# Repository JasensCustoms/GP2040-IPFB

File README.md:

The <a href="https://jasenscustoms.com/collections/fight-stick-pcbs/products/integrated-pico-fighting-board-gp2040ce">Integrated Pico Fighting Board</a> is an open source arcade fight stick PCB design made available under the Creative Commons Attribution-Non Commercial Sharealike 4.0 International License. This is a solely **hardware** project that is designed to easily run **unmodified** GP2040-CE firmware. That has always been the intent despite narratives suggesting otherwise.

It was designed to follow the Fighting Game Community Layout Generally Accepted Standard originally pioneered by AkiShop. This design was adopted by Brook for most of their fighting boards at the behest and urging of myself and a few other makers in the space early in Brook's entry to the market. The goal was to make the IPFB a low cost, easy drop-in in replacement for the PS360+ or any Brook Board if a person so chose.

## Design Files

All design files are made using Autodesk EagleCAD and will only be published in that format. Gerbers and Centroids will not be provided. A basic BOM will also be provided. This is to allow hobbyists with some design experience to use their choice of board house to produce their PCBs. There are many to chose from, and it is not our intent to influence your choice. All files are provided as-is without any guarantee of support or help. 

## Sale Channels

Note: The only entity that may sell the Integrated Pico Fighting Board Design is at the link above. If you wish to offer this design commercially, please reach out to [jasenhicks@jasenscustoms.com ](mailto:jasenhicks@jasenscustoms.com). If others are approved to sell the design, they will be listed here. I encourage you to inform me if you see unapproved commercial sale of the IPFB. As of now, I have chosen to stop production of the IPFB. A full discussion can be found on our discord, linked below.

## GPIO Settings 

Main Buttons and Directions:

- GPIO 0: Left
- GPIO 1: Up
- GPIO 2: Down
- GPIO 3: Right
- GPIO 4: HOME (PS)
- GPIO 5: SELECT (SHARE)
- GPIO 6: START
- GPIO 7: Punch 1
- GPIO 8: Punch 2
- GPIO 9: Punch 3
- GPIO 10: Punch 4
- GPIO 11: Kick 1
- GPIO 12: Kick 2
- GPIO 13: Kick 3
- GPIO 14: Kick 4

RGB Data Channel

- GPIO 15: RGB Data

Player LEDS (Version 2.0+ PCB can designate these as other functions as the resistor on the line has been removed)

- GPIO 16: Player 1 LED
- GPIO 17: Player 2 LED
- GPIO 18: Player 3 LED
- GPIO 19: Player 4 LED

Modern Controller Buttons, Turbo Functions

- GPIO 20: Touch Pad Click
- GPIO 21: L3
- GPIO 22: R3
- GPIO 23: TURBO LED (Version 2.0+ PCB can designate this as another function as the resistor on the line has been removed)
- GPIO 28: TURBO KEY

I2C Lines both have been pulled high via resistor (3.3V)

- GPIO 26: SDA
- GPIO 27: SCL

USB Passthrough GPIO

- GPIO 24: DATA PLUS
- GPIO 25: DATA MINUS

## Firmware

No custom firmware is needed or provided for the Integrated Pico Fighting Board. Because the pin definitions are derived from FeralAI's carrier board, firmware for the Pico Fighting Board is expected to be compatible with minimal settings changes. Steps to customize GP2040-CE settings to fully utilize Turbo and Playstation authentication are indicated below.

### Settings
To manually adust the PicoFightingBoard firmware to work perfectly with the IPFB, just adjust these settings.

#### Turbo
- Add on Configuration:
  - Enable turbo
  - Turbo LED Pin 23
  - Save
- Pin Mappings:
  - Set pin 28 to Turbo
  - Save

#### PS5 (or PS4)
- Input Mode Settings
  - Current Input Mode: PS5 (or PS4)
  - Authentication Settings: Host USB
- Boot Input Modes
  - Set B4 to PS5 (or PS4)

#### XBone
- Boot Input Modes
  - Set R1 to XBone

## Support

All files are provided as is and without warranty.

For issues with Integrated Pico Fight Board hardware that was bought and sold via JasensCustoms.com, please reach out via [Jasen's Customs Discord](https://discord.gg/M9E8PFHSCm).

To discuss GP2040-CE firmware including features, issues, or anything else please join the [OpenStick GP2040-CE Discord](https://discord.gg/k2pxhke7q8) or [create a GitHub issue](https://github.com/OpenStickCommunity/GP2040-CE/issues/new).

Hardware change suggestions can be submitted as GitHub issues on this repository, and will be reviewed on a case by case basis by the JasensCustoms.com team. Not all suggestions will be implemented.

## Acknolwedgements

- [RegentOfOrigin](https://github.com/RegentOfOrigin) for helping manage the GitHub
- [wrennnnnn](https://github.com/wrennnnnn). for the initial management and compiling of the FW with the IPFB Config.h file
- [The entire Open Stick Community](https://github.com/OpenStickCommunity) for the GP2040-CE firmware
- Particularly [FeralAI](https://github.com/FeralAI) for the initial work in designing and making the [PicoFightingBoard](https://github.com/FeralAI/PicoFightingBoard) available

Copyright for the Pico Fighting Board is held by FeralAI, 2021.
Copyright for GP2040-CE is held by The Open Stick Community, 2024.

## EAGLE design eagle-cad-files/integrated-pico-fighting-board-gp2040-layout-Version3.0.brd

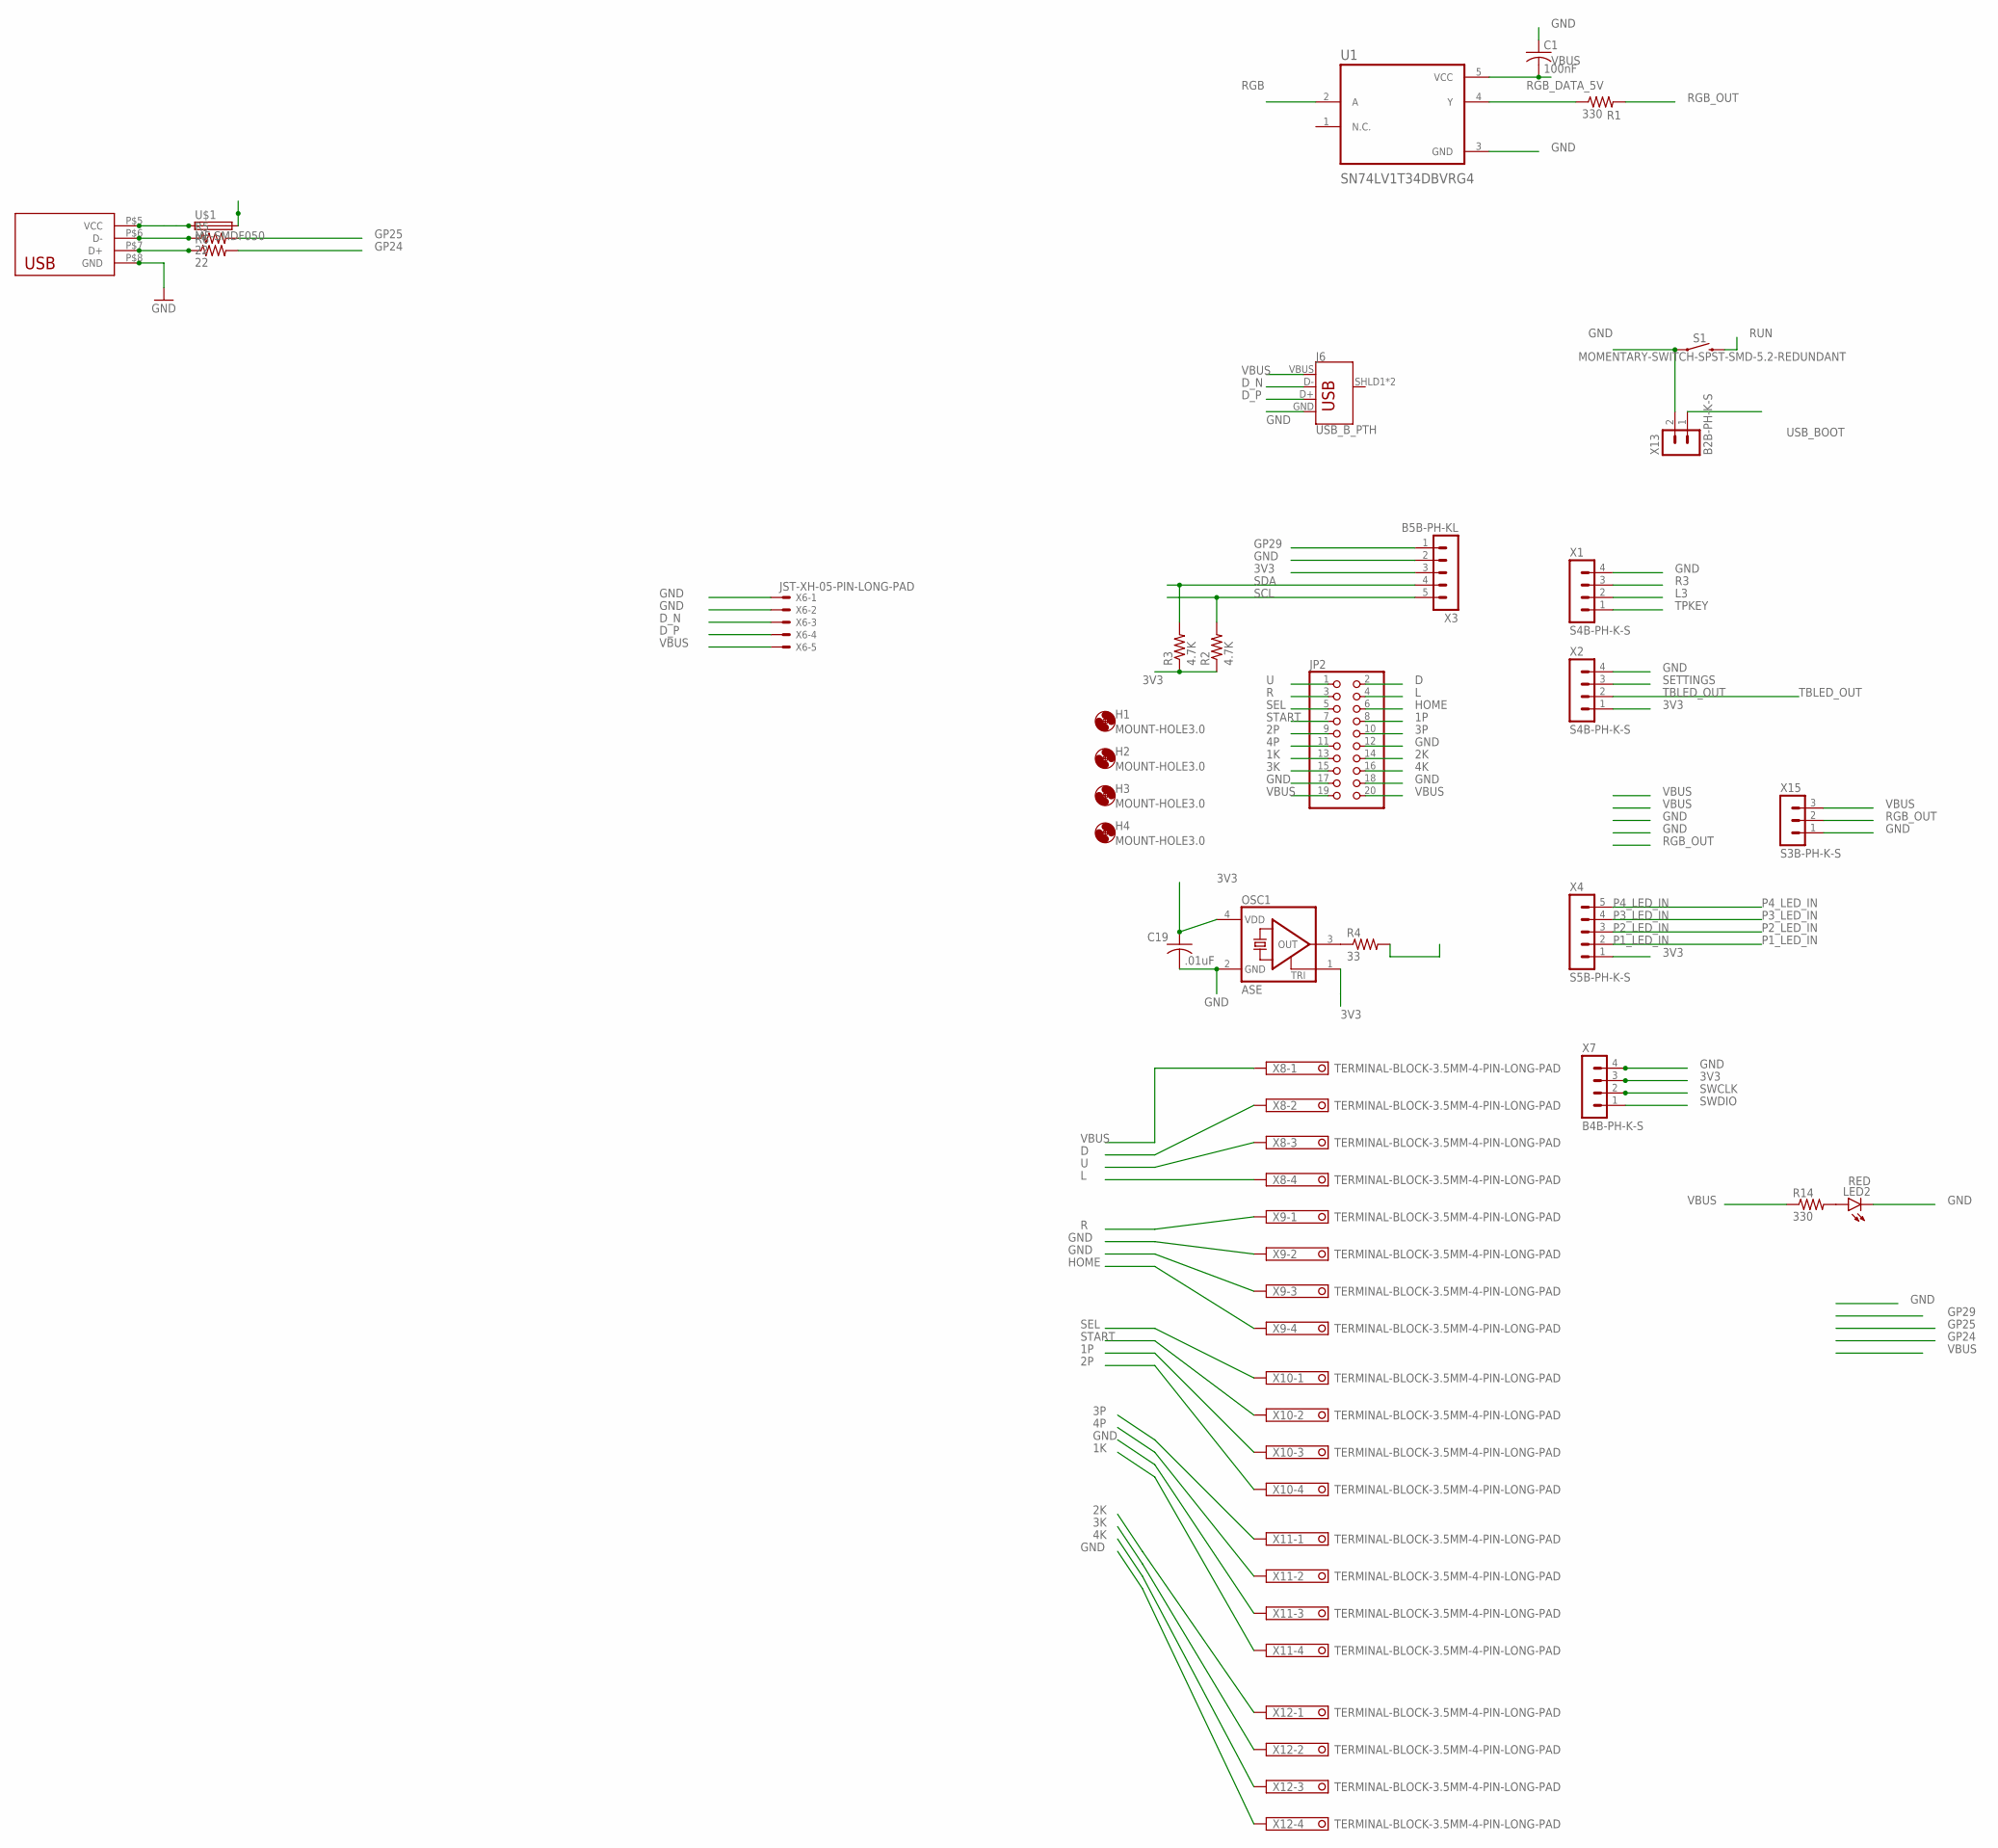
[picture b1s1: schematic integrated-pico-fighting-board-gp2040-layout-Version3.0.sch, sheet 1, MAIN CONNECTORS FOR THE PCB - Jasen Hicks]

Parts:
C1: 100nF; C0603K
C19: .01uF; C0402K
H1, H2, H3, H4: MOUNT-HOLE3.0; 3,0
J6: USB_B_PTH; USB-B-PTH
JP2: PINHD-2X10; 2X10
LED2: RED; CHIP-LED0603
OSC1: ASE
R1, R14: 330; R0603
R2, R3: 4.7K; R0603
R4: 33; R0402
R5, R6: 22; R0805
S1: MOMENTARY-SWITCH-SPST-SMD-5.2-REDUNDANT; TACTILE_SWITCH_SMD_5.2MM
U1: SN74LV1T34DBVRG4; SOT95P280X145-5N
U$1: MF-SMDF050
U$2: USB-302S
X1, X2: S4B-PH-K-S
X3: B5B-PH-KL; B5B-PH-K-S
X4: S5B-PH-K-S
X6: JST-XH-05-PIN-LONG-PAD; JST-XH-05-PACKAGE-LONG-PAD
X7: B4B-PH-K-S
X8, X9, X10, X11, X12: TERMINAL-BLOCK-3.5MM-4-PIN-LONG-PAD; TERMINAL-BLOCK-4-PIN-3.5MM-LONG-PAD
X13: B2B-PH-K-S
X15: S3B-PH-K-S

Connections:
1K: JP2.13, X11.4; also elsewhere on the board
1P: JP2.8, X10.3; also elsewhere on the board
2K: JP2.14, X12.1; also elsewhere on the board
2P: JP2.9, X10.4; also elsewhere on the board
3K: JP2.15, X12.2; also elsewhere on the board
3P: JP2.10, X11.1; also elsewhere on the board
3V3: C19.1, OSC1.1 (TRI), OSC1.4 (VDD), R2.1, R3.1, X2.1, X3.3, X4.1, X7.3; also elsewhere on the board
4K: JP2.16, X12.3; also elsewhere on the board
4P: JP2.11, X11.2; also elsewhere on the board
D: JP2.2, X8.2; also elsewhere on the board
D_N: J6.D-, X6.3; also elsewhere on the board
D_P: J6.D+, X6.4; also elsewhere on the board
GND: C1.1, C19.2, J6.GND, JP2.12, JP2.17, JP2.18, LED2.C, OSC1.2 (GND), S1.1, S1.2 (1), U1.3 (GND), U$2.P$8 (GND), X1.4, X2.4, X3.2, X6.1, X6.2, X7.4, X9.2, X9.3, X11.3, X12.4, X13.2, X15.1; also elsewhere on the board
GP24: R6.2; also elsewhere on the board
GP25: R5.2; also elsewhere on the board
GP29: X3.1; also elsewhere on the board
HOME: JP2.6, X9.4; also elsewhere on the board
L: JP2.4, X8.4; also elsewhere on the board
L3: X1.2; also elsewhere on the board
unnamed: OSC1.3 (OUT), R4.1
unnamed: LED2.A, R14.2
unnamed: U$1.1, U$2.P$5 (VCC)
unnamed: R5.1, U$2.P$6 (D-)
unnamed: R6.1, U$2.P$7 (D+)
P1_LED_IN: X4.2; also elsewhere on the board
P2_LED_IN: X4.3; also elsewhere on the board
P3_LED_IN: X4.4; also elsewhere on the board
P4_LED_IN: X4.5; also elsewhere on the board
R: JP2.3, X9.1; also elsewhere on the board
R3: X1.3; also elsewhere on the board
RGB: U1.2 (A); also elsewhere on the board
RGB_DATA_5V: R1.1, U1.4 (Y)
RGB_OUT: R1.2, X15.2
RUN: S1.3 (2), S1.4 (2); also elsewhere on the board
SCL: R2.2, X3.5; also elsewhere on the board
SDA: R3.2, X3.4; also elsewhere on the board
SEL: JP2.5, X10.1; also elsewhere on the board
SETTINGS: X2.3; also elsewhere on the board
START: JP2.7, X10.2; also elsewhere on the board
SWCLK: X7.2; also elsewhere on the board
SWDIO: X7.1; also elsewhere on the board
TBLED_OUT: X2.2; also elsewhere on the board
TPKEY: X1.1; also elsewhere on the board
U: JP2.1, X8.3; also elsewhere on the board
USB_BOOT: X13.1; also elsewhere on the board
VBUS: C1.2, J6.VBUS, JP2.19, JP2.20, R14.1, U1.5 (VCC), U$1.2, X6.5, X8.1, X15.3; also elsewhere on the board
XIN: R4.2; also elsewhere on the board

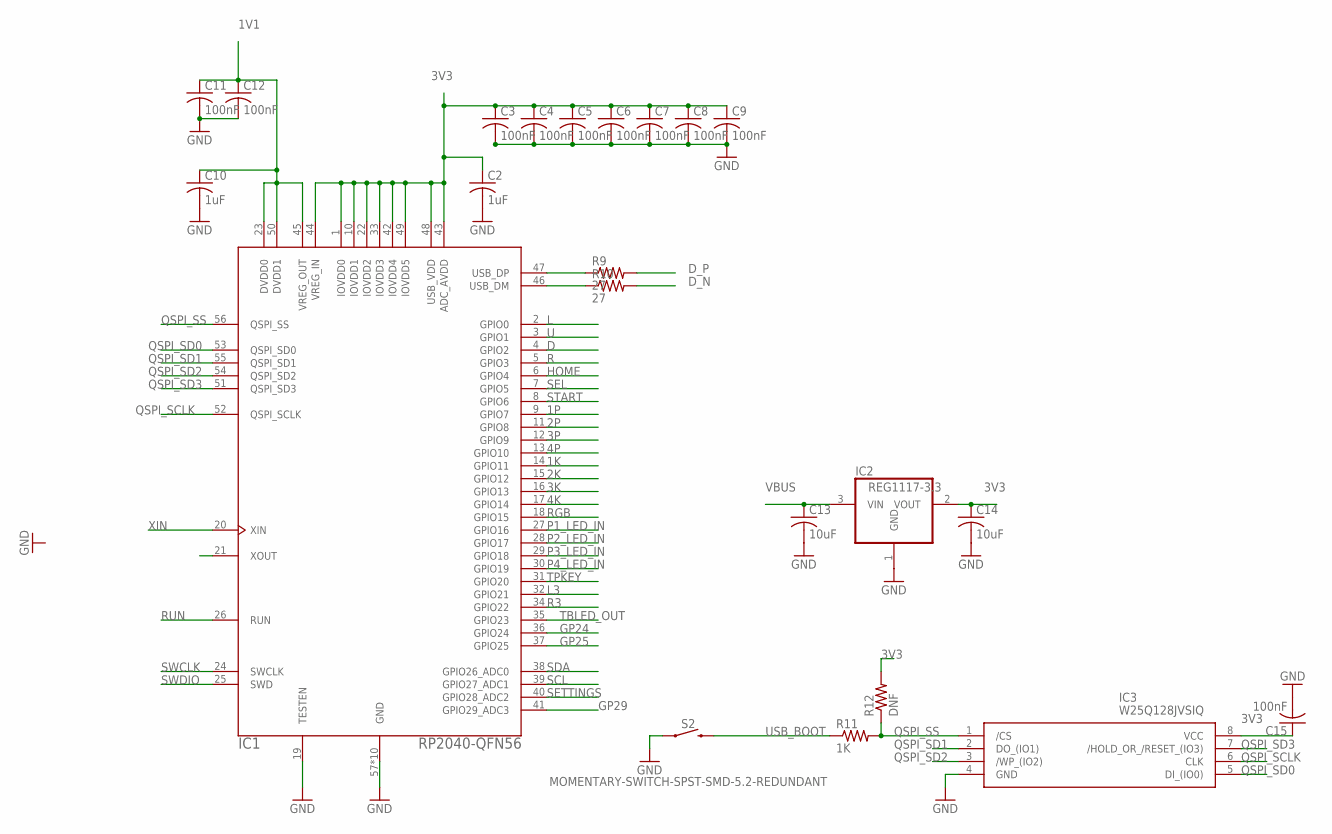
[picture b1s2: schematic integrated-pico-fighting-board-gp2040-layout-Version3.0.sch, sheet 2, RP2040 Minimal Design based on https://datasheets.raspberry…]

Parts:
C2, C10: 1uF; C0402K
C3, C4, C5, C6, C7, C8, C9, C11, C12, C15: 100nF; C0402K
C13, C14: 10uF; C0402K
IC1: RP2040-QFN56; RP2040-QFN-56
IC2: REG1117-3.3; SOT223
IC3: W25Q128JVSIQ; SOIC127P790X216-8N
R9, R10: 27; R0402
R11: 1K; R0402
R12: DNF; R0402
S2: MOMENTARY-SWITCH-SPST-SMD-5.2-REDUNDANT; TACTILE_SWITCH_SMD_5.2MM

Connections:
1K: IC1.14 (GPIO11); also elsewhere on the board
1P: IC1.9 (GPIO7); also elsewhere on the board
1V1: C10.1, C11.1, C12.1, IC1.23 (DVDD0), IC1.45 (VREG_OUT), IC1.50 (DVDD1)
2K: IC1.15 (GPIO12); also elsewhere on the board
2P: IC1.11 (GPIO8); also elsewhere on the board
3K: IC1.16 (GPIO13); also elsewhere on the board
3P: IC1.12 (GPIO9); also elsewhere on the board
3V3: C2.1, C3.1, C4.1, C5.1, C6.1, C7.1, C8.1, C9.1, C14.1, C15.1, IC1.1 (IOVDD0), IC1.10 (IOVDD1), IC1.22 (IOVDD2), IC1.33 (IOVDD3), IC1.42 (IOVDD4), IC1.43 (ADC_AVDD), IC1.44 (VREG_IN), IC1.48 (USB_VDD), IC1.49 (IOVDD5), IC2.2 (VOUT), IC3.8 (VCC), R12.2; also elsewhere on the board
4K: IC1.17 (GPIO14); also elsewhere on the board
4P: IC1.13 (GPIO10); also elsewhere on the board
D: IC1.4 (GPIO2); also elsewhere on the board
D_N: R10.2; also elsewhere on the board
D_P: R9.2; also elsewhere on the board
GND: C2.2, C3.2, C4.2, C5.2, C6.2, C7.2, C8.2, C9.2, C10.2, C11.2, C12.2, C13.2, C14.2, C15.2, IC1.19 (TESTEN), IC1.57 (GND), IC1.58 (GND), IC1.59 (GND), IC1.60 (GND), IC1.61 (GND), IC1.62 (GND), IC1.63 (GND), IC1.64 (GND), IC1.65 (GND), IC1.66 (GND), IC2.1 (GND), IC3.4 (GND), S2.1, S2.2 (1); also elsewhere on the board
GP24: IC1.36 (GPIO24); also elsewhere on the board
GP25: IC1.37 (GPIO25); also elsewhere on the board
GP29: IC1.41 (GPIO29_ADC3); also elsewhere on the board
HOME: IC1.6 (GPIO4); also elsewhere on the board
L: IC1.2 (GPIO0); also elsewhere on the board
L3: IC1.32 (GPIO21); also elsewhere on the board
unnamed: IC1.47 (USB_DP), R9.1
unnamed: IC1.46 (USB_DM), R10.1
P1_LED_IN: IC1.27 (GPIO16); also elsewhere on the board
P2_LED_IN: IC1.28 (GPIO17); also elsewhere on the board
P3_LED_IN: IC1.29 (GPIO18); also elsewhere on the board
P4_LED_IN: IC1.30 (GPIO19); also elsewhere on the board
QSPI_SCLK: IC1.52 (QSPI_SCLK), IC3.6 (CLK)
QSPI_SD0: IC1.53 (QSPI_SD0), IC3.5 (DI_(IO0))
QSPI_SD1: IC1.55 (QSPI_SD1), IC3.2 (DO_(IO1))
QSPI_SD2: IC1.54 (QSPI_SD2), IC3.3 (/WP_(IO2))
QSPI_SD3: IC1.51 (QSPI_SD3), IC3.7 (/HOLD_OR_/RESET_(IO3))
QSPI_SS: IC1.56 (QSPI_SS), IC3.1 (/CS), R11.2, R12.1
R: IC1.5 (GPIO3); also elsewhere on the board
R3: IC1.34 (GPIO22); also elsewhere on the board
RGB: IC1.18 (GPIO15); also elsewhere on the board
RUN: IC1.26 (RUN); also elsewhere on the board
SCL: IC1.39 (GPIO27_ADC1); also elsewhere on the board
SDA: IC1.38 (GPIO26_ADC0); also elsewhere on the board
SEL: IC1.7 (GPIO5); also elsewhere on the board
SETTINGS: IC1.40 (GPIO28_ADC2); also elsewhere on the board
START: IC1.8 (GPIO6); also elsewhere on the board
SWCLK: IC1.24 (SWCLK); also elsewhere on the board
SWDIO: IC1.25 (SWD); also elsewhere on the board
TBLED_OUT: IC1.35 (GPIO23); also elsewhere on the board
TPKEY: IC1.31 (GPIO20); also elsewhere on the board
U: IC1.3 (GPIO1); also elsewhere on the board
USB_BOOT: R11.1, S2.3 (2), S2.4 (2); also elsewhere on the board
VBUS: C13.1, IC2.3 (VIN); also elsewhere on the board
XIN: IC1.20 (XIN); also elsewhere on the board

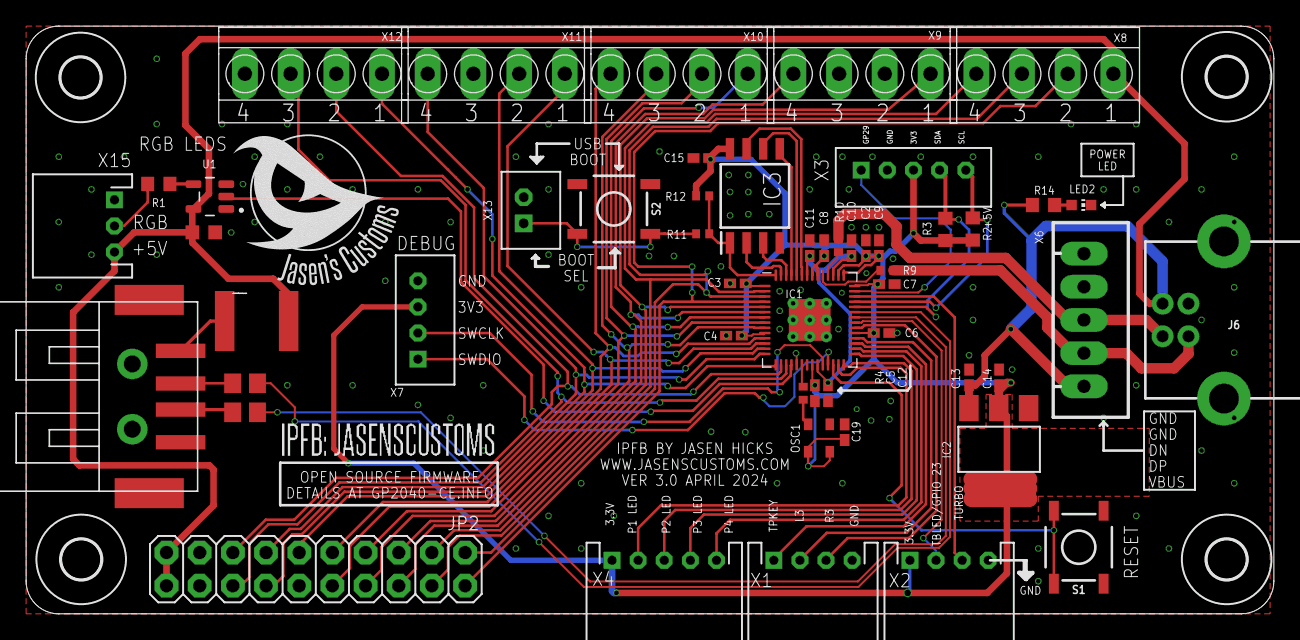
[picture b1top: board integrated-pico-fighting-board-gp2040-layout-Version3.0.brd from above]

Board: 2 copper layers, 95.5 x 45.0 mm, 56 parts (0 on the bottom side), 56 nets.

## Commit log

2024-08-25 Integrated Pico Fighting Board config & README
2024-08-25 Automate release process
2024-08-25 Check upstream twice a month
2024-08-25 Properly check that release version exists
2024-08-25 Update auto-generated release's notes
2024-09-18 Correct LICENSE with approval from @jasenscustoms, include copyright notice in README, update README to clarify project intent and separation from GP2040-CE
2024-10-10 Remove unnecessary config options from BoardConfig
2024-10-10 Test - Isolate differences
2025-02-02 Stop building firmware
2025-02-02 Update LICENSE
2025-02-02 Remove all GP2040 files and finish updating readme.

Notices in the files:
parts and their libraries:
SparkFun-Connectors: Licensing: Creative Commons ShareAlike 4.0 International - https://creativecommons.org/licenses/by-sa/4.0
